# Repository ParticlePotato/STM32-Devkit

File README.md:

# STM32G474RETx DevKit

A compact, 40-pin breadboard-friendly development board based on the high-performance **STM32G474RETx** microcontroller (LQFP64). Designed for advanced analog applications, digital power control, and versatile prototyping.

## 🚀 Key Features
* **MCU:** STM32G474RETx (Arm® Cortex®-M4 with FPU, 170 MHz, 512 KB Flash)
* **Crystal:** 16Mhz
* **Form Factor:** 40-pin dual-row header layout (2x20 pins)
* **Power Supply:** Dual rail design (+5V and +3V3 LDO output) via Micro USB or external pins
* **Hardware Safe:** Integrated input diode protection and power state LED indicator
* **Debug Support:** Standard SWD interface header (SWDIO, SWCLK, SWO, NRST)
* **User Control:** Onboard Reset button (SW1) and Boot selector (SW2)

## 🛠️ Hardware Design Architecture

### 1. Power Distribution & Regulation
* **LDO Regulator:** High-efficiency **AMS1117-3.3** drops the incoming +5V rail down to a stable +3V3 for the MCU logic.
* **Decoupling Network:** Dedicated 100nF ceramic capacitors placed adjacent to every individual VDD pin.
* **Analog Isolation:** **VDDA** and **VREF+** lines are isolated from the main digital power rail using a ferrite bead (FB2) and a 100nF/1uF capacitor array to maintain low-noise ADC/DAC precision.

### 2. Clock & System Controls
* **Main Clock (HSE):** Driven by an external 16 MHz crystal oscillator setup with 18pF load capacitors for stable system timing.
* **Boot Configuration:** BOOT0 pin is tied to GND via a 10kΩ resistor for default Flash booting, accessible via a dedicated switch (SW2).

## 📌 Header Pinout Layout

### Connector J2 (Left Header)
* **Pin 1:** +3V3
* **Pins 2:** GND
* **Pins 3:** VBUS
* **Pin 4:** ADC/TIM
* **Pins 5:** ADC/TIM
* **Pins 6:** ADC/TIM
* **Pin 7:** ADC/TIM
* **Pins 8:** ADC/TIM
* **Pins 9:** ADC/TIM
* **Pin 10:** ADC/TIM
* **Pins 11:** ADC/TIM
* **Pins 12:** ADC/TIM
* **Pin 13:** ADC/TIM
* **Pins 14:** ADC/TIM
* **Pins 15:** ADC/TIM
* **Pins 16:** ADC/TIM
* **Pins 17:** ADC/TIM
* **Pin 18:** TIM
* **Pins 19:** TIM
* **Pins 20:** TIM

### Connector J6 (Right Header)
* **Pin 1:** +3V3
* **Pins 2:** GND
* **Pins 3:** +5V 
* **Pin 4:** UART/ADC/TIM
* **Pins 5:** UART/TIM
* **Pins 6:** I2C/TIM
* **Pin 7:** I2C/ADC/TIM
* **Pins 8:** ADC/TIM
* **Pins 9:** ADC/TIM
* **Pin 10:** ADC/TIM
* **Pins 11:** ADC/TIM
* **Pins 12:** ADC/TIM
* **Pin 13:** ADC/TIM
* **Pins 14:** TIM
* **Pins 15:** TIM
* **Pins 16:** ADC/TIM
* **Pins 17:** TIM
* **Pin 18:** TIM/GPIO
* **Pins 19:** GPIO(0v or 3.3v)
* **Pins 20:** GPIO(0v or 3.3v)

## 📄 License
This project is open-source and released under the [MIT License](LICENSE).

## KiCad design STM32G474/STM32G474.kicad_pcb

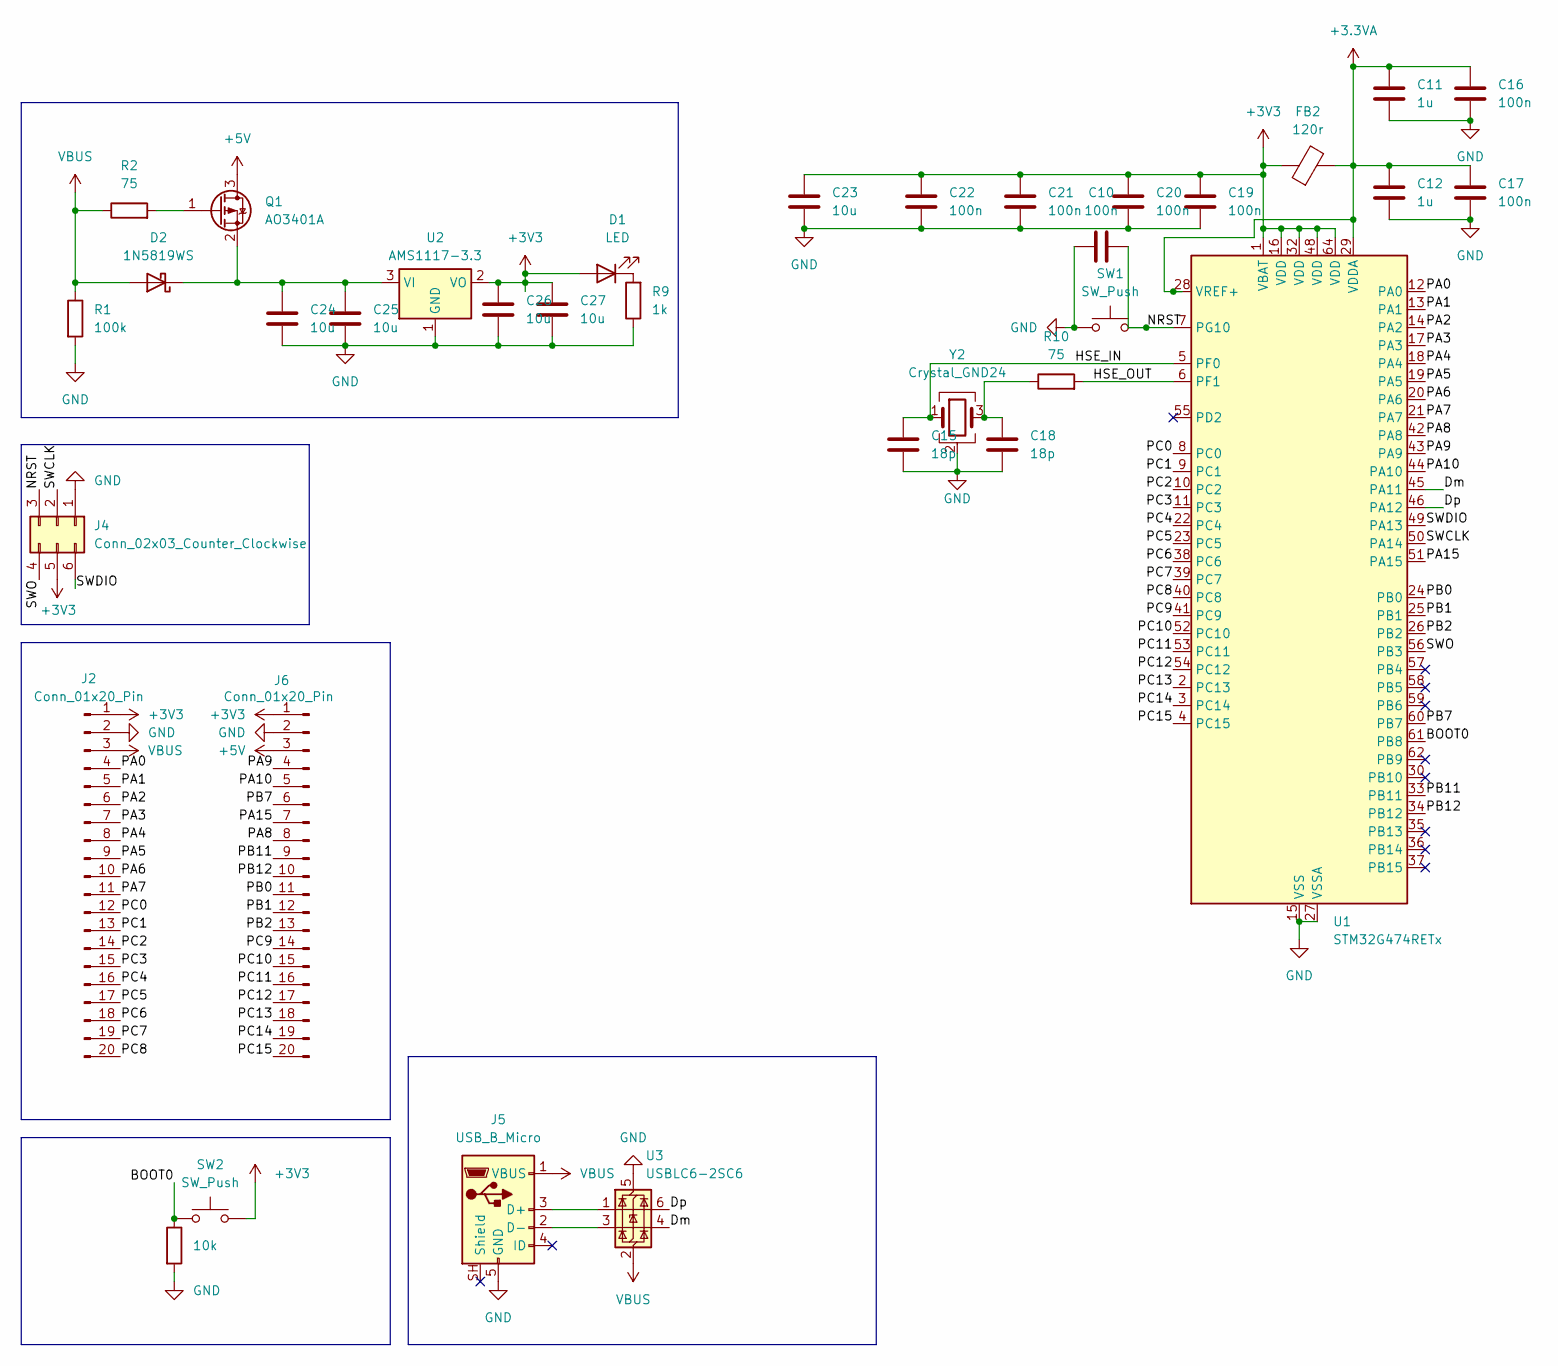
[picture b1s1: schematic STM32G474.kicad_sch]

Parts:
C10, C16, C17, C19, C20, C21, C22: 100n; C_0805_2012Metric_Pad1.18x1.45mm_HandSolder; LCSC C49678
C11, C12: 1u; C_0805_2012Metric_Pad1.18x1.45mm_HandSolder; LCSC C15849
C15, C18: 18p; C_0805_2012Metric_Pad1.18x1.45mm_HandSolder; LCSC C113825
C23, C24, C25, C26, C27: 10u; C_0805_2012Metric_Pad1.18x1.45mm_HandSolder; LCSC C15850
D1: LED; LED_0805_2012Metric_Pad1.15x1.40mm_HandSolder; LCSC C84260
D2: 1N5819WS; D_SOD-323_HandSoldering; LCSC C191023
FB2: 120r; L_0805_2012Metric_Pad1.05x1.20mm_HandSolder; LCSC C15957
J2, J6: Conn_01x20_Pin; PinHeader_1x20_P2.54mm_Vertical
J4: Conn_02x03_Counter_Clockwise; PinSocket_2x03_P2.54mm_Vertical
J5: USB_B_Micro; USB_Micro-AB_Molex_47590-0001; LCSC C136001
Q1: AO3401A; SOT-23_Handsoldering; LCSC C347476
R1: 100k; R_0805_2012Metric_Pad1.20x1.40mm_HandSolder; LCSC C149504
R2, R10: 75; R_0805_2012Metric_Pad1.20x1.40mm_HandSolder; LCSC C2933498
R9: 1k; R_0805_2012Metric_Pad1.20x1.40mm_HandSolder; LCSC C17513
R11: 10k; R_0805_2012Metric_Pad1.20x1.40mm_HandSolder; LCSC C17414
SW1, SW2: SW_Push; SW_Push_SPST_NO_Alps_SKRK; LCSC C262416
U1: STM32G474RETx; LQFP-64_10x10mm_P0.5mm; LCSC C521608
U2: AMS1117-3.3; SOT-223-3_TabPin2; LCSC C6186
U3: USBLC6-2SC6; SOT-23-6_Handsoldering; LCSC C7519
Y2: Crystal_GND24; Crystal_SMD_3225-4Pin_3.2x2.5mm_HandSoldering; LCSC C12668

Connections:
+3.3VA: C11.1, C12.1, C16.1, C17.1, FB2.2, U1.28 (VREF+), U1.29 (VDDA)
+3V3: C19.1, C20.1, C21.1, C22.1, C23.1, C26.1, C27.1, D1.2 (A), FB2.1, J2.1, J4.5, J6.1, SW2.2, U1.1 (VBAT), U1.16 (VDD), U1.32 (VDD), U1.48 (VDD), U1.64 (VDD), U2.2 (VO)
+5V: J6.3, Q1.3 (D)
/BOOT0: R11.1, SW2.1, U1.61 (PB8)
/Dm: U1.45 (PA11), U3.4 (I/O2)
/Dp: U1.46 (PA12), U3.6 (I/O1)
/HSE_IN: C15.1, U1.5 (PF0), Y2.1
/HSE_OUT: R10.2, U1.6 (PF1)
/NRST: C10.2, J4.3, SW1.2, U1.7 (PG10)
/PA0: J2.4, U1.12 (PA0)
/PA1: J2.5, U1.13 (PA1)
/PA2: J2.6, U1.14 (PA2)
/PA3: J2.7, U1.17 (PA3)
/PA4: J2.8, U1.18 (PA4)
/PA5: J2.9, U1.19 (PA5)
/PA6: J2.10, U1.20 (PA6)
/PA7: J2.11, U1.21 (PA7)
/PA8: J6.8, U1.42 (PA8)
/PA9: J6.4, U1.43 (PA9)
/PA10: J6.5, U1.44 (PA10)
/PA15: J6.7, U1.51 (PA15)
/PB0: J6.11, U1.24 (PB0)
/PB1: J6.12, U1.25 (PB1)
/PB2: J6.13, U1.26 (PB2)
/PB7: J6.6, U1.60 (PB7)
/PB11: J6.9, U1.33 (PB11)
/PB12: J6.10, U1.34 (PB12)
/PC0: J2.12, U1.8 (PC0)
/PC1: J2.13, U1.9 (PC1)
/PC2: J2.14, U1.10 (PC2)
/PC3: J2.15, U1.11 (PC3)
/PC4: J2.16, U1.22 (PC4)
/PC5: J2.17, U1.23 (PC5)
/PC6: J2.18, U1.38 (PC6)
/PC7: J2.19, U1.39 (PC7)
/PC8: J2.20, U1.40 (PC8)
/PC9: J6.14, U1.41 (PC9)
/PC10: J6.15, U1.52 (PC10)
/PC11: J6.16, U1.53 (PC11)
/PC12: J6.17, U1.54 (PC12)
/PC13: J6.18, U1.2 (PC13)
/PC14: J6.19, U1.3 (PC14)
/PC15: J6.20, U1.4 (PC15)
/SWCLK: J4.2, U1.50 (PA14)
/SWDIO: J4.6, U1.49 (PA13)
/SWO: J4.4, U1.56 (PB3)
GND: C10.1, C11.2, C12.2, C15.2, C16.2, C17.2, C18.2, C19.2, C20.2, C21.2, C22.2, C23.2, C24.2, C25.2, C26.2, C27.2, J2.2, J4.1, J5.5 (GND), J6.2, R1.2, R9.1, R11.2, SW1.1, U1.15 (VSS), U1.27 (VSSA), U1.31 (VSS), U1.47 (VSS), U1.63 (VSS), U2.1 (GND), U3.5 (VBUS), Y2.2 (G), Y2.4 (G)
unnamed: C18.1, R10.1, Y2.3
unnamed: D1.1 (K), R9.2
unnamed: C24.1, C25.1, D2.1 (K), Q1.2 (S), U2.3 (VI)
unnamed: J5.3 (D+), U3.1 (I/O1)
unnamed: J5.2 (D-), U3.3 (I/O2)
unnamed: Q1.1 (G), R2.2
VBUS: D2.2 (A), J2.3, J5.1 (VBUS), R1.1, R2.1, U3.2 (GND)

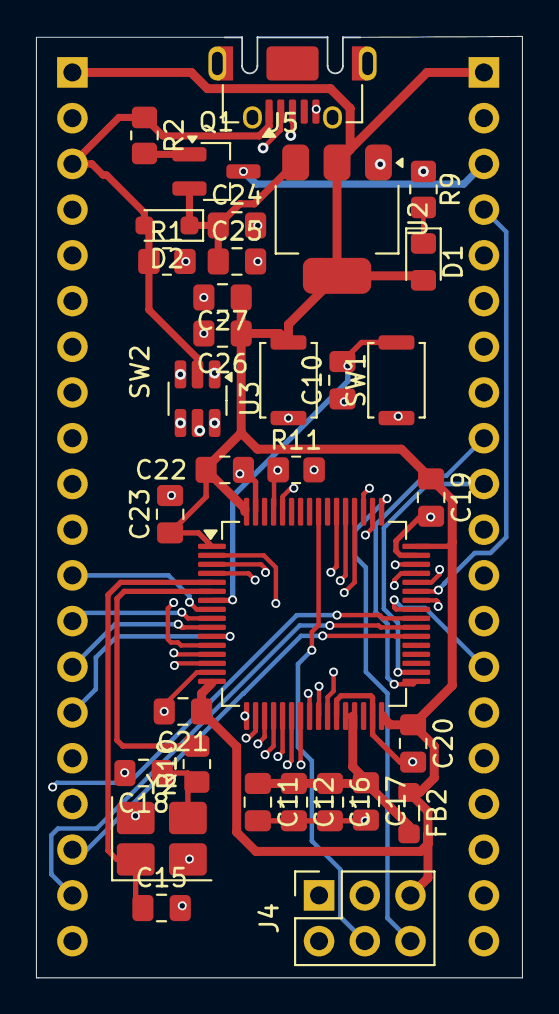
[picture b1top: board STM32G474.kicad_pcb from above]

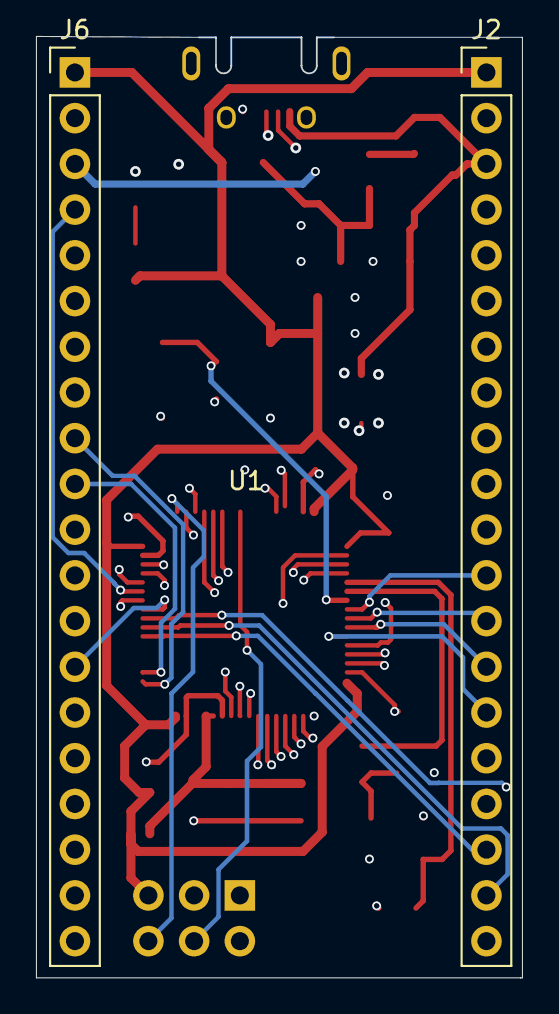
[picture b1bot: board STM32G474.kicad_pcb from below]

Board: 4 copper layers, 27.0 x 52.3 mm, 35 parts (2 on the bottom side), 54 nets.

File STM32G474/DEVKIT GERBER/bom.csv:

Designator,Footprint,Quantity,Value,LCSC Part #
"C10, C16, C17, C19, C20, C21, C22",0805,7,100n,C49678
"C11, C12",0805,2,1u,C15849
"C13, C14",0805,2,22u,C602037
"C15, C18",0805,2,18p,C113825
C23,0805,1,10u,C15850
D1,0805,1,LED,C84260
D2,D_SOD-323_HandSoldering,1,1N5819WS,C191023
FB2,0805,1,120r,C15957
"J2, J6",PinHeader_1x20_P2.54mm_Vertical,2,Conn_01x20_Pin,
J4,PinSocket_2x03_P2.54mm_Vertical,1,Conn_02x03_Counter_Clockwise,
J5,USB_Micro-AB_Molex_47590-0001,1,USB_B_Micro,C136001
Q1,SOT-23_Handsoldering,1,AO3401A,C347476
R1,0805,1,100k,C149504
R10,0805,1,75,C2933498
R11,0805,1,10k,C17414
R2,0805,1,100,C17408
R9,0805,1,1k,C17513
"SW1, SW2",SW_Push_SPST_NO_Alps_SKRK,2,SW_Push,C262416
U1,LQFP-64_10x10mm_P0.5mm,1,STM32G474RETx,C521608
U2,SOT-223-3_TabPin2,1,AMS1117-3.3,C6186
Y2,Crystal_SMD_3225-4Pin_3.2x2.5mm_HandSoldering,1,Crystal_GND24,C12668

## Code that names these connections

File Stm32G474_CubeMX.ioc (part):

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Mcu.Name=STM32G474R(B-C-E)Tx
Mcu.Package=LQFP64
Mcu.UserName=STM32G474RETx
PA11.Mode=Device
PA11.Signal=USB_DM
PA12.Mode=Device
PA12.Signal=USB_DP
PA13.Mode=Trace_Asynchronous_SW
PA13.Signal=SYS_JTMS-SWDIO
PA14.Mode=Trace_Asynchronous_SW
PA14.Signal=SYS_JTCK-SWCLK
PB3.Mode=Trace_Asynchronous_SW
PB3.Signal=SYS_JTDO-SWO
PF0-OSC_IN.Mode=HSE-External-Oscillator
PF0-OSC_IN.Signal=RCC_OSC_IN
PF1-OSC_OUT.Mode=HSE-External-Oscillator
PF1-OSC_OUT.Signal=RCC_OSC_OUT
RCC.HSE_VALUE=16000000
RCC.SYSCLKFreq_VALUE=170000000
RCC.SYSCLKSource=RCC_SYSCLKSOURCE_PLLCLK
board=custom
